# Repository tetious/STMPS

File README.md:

STMPS
=====

**STMPS** is a WIP 3d printer board based around the STM32f411, with inspiration and guidance
from the Printrboard, RAMPS 1.4, and the RepRap project.

**ALPHA-3**

This board is intended to work with Ambroz Bizjak's astonishingly fantastic 
[aprinter](https://github.com/ambrop72/aprinter) firmware. Configuration files and guidance will be
provided once the board is further along.

STMPS is open source hardware, licensed under CC BY-SA. Copyright (C) 2016 Greg Lincoln.

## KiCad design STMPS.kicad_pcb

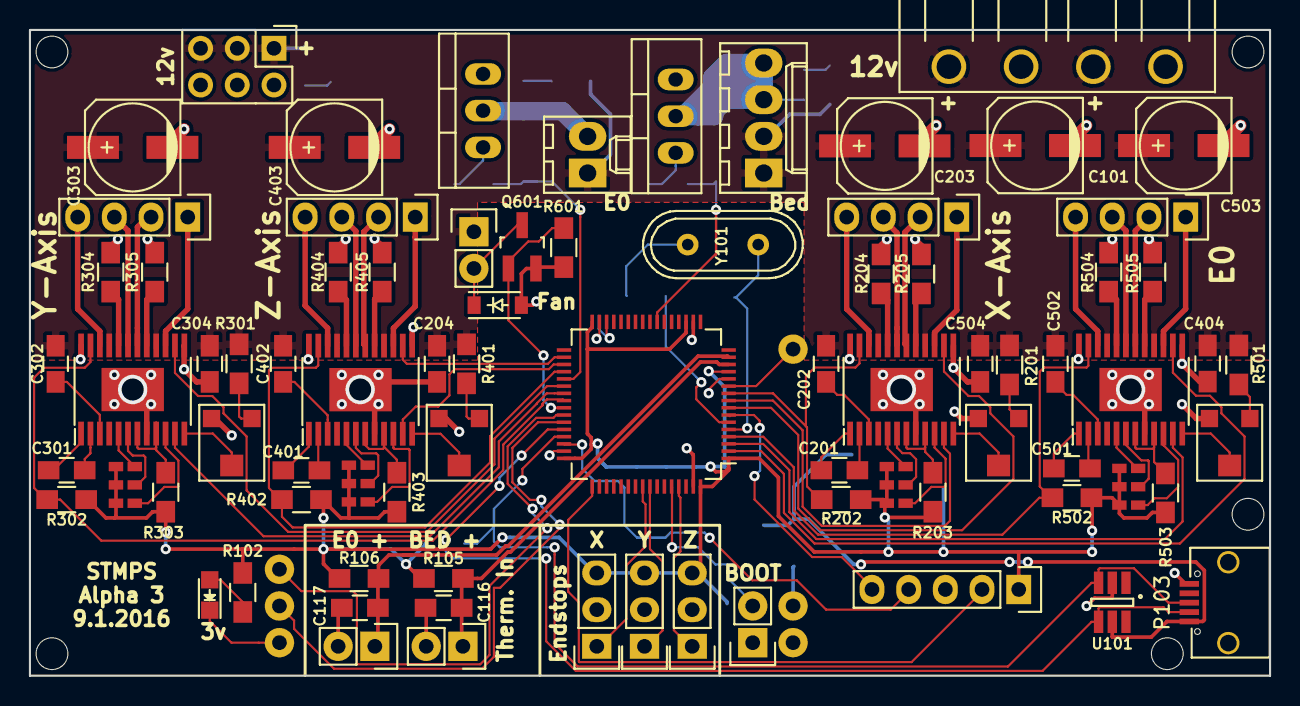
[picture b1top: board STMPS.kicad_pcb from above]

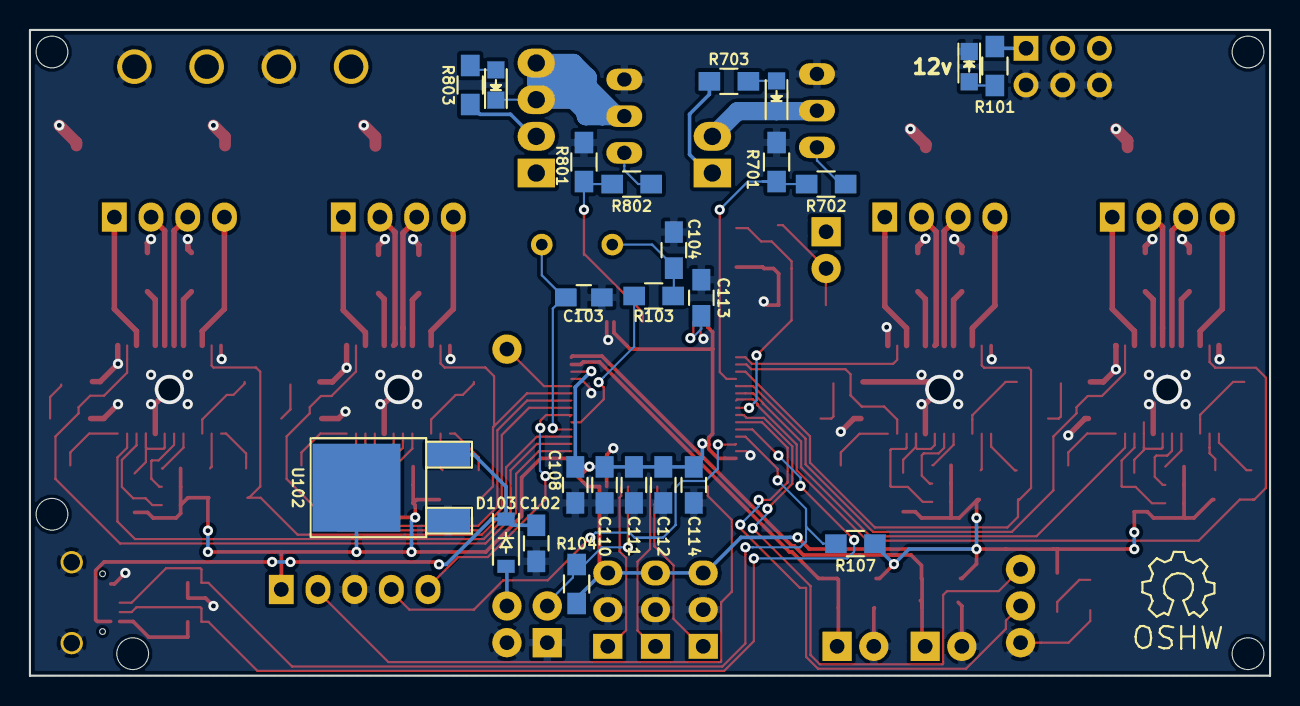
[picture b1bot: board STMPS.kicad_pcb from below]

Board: 2 copper layers, 85.9 x 44.7 mm, 113 parts (24 on the bottom side), 107 nets.

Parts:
C101, C203, C303, C403, C503: 100uf; c_elec_6.3x5.8
C102, C116, C117: 10uf; C_0805_HandSoldering
C103, C104: 20pf; C_0805_HandSoldering
C108, C110, C111, C112: 100nf; C_0805_HandSoldering
C113, C114: 4.7uf; C_0805_HandSoldering
C201, C202, C204, C301, C302, C304, C401, C402, C404, C501, C502, C504: 0.1uf; C_0805_HandSoldering
D101: 12v_PWR; LED_0805
D102: 3v_PWR; LED_0805
D103, D601: D_Schottky_Small; SOD-123
D701, D801: r; LED_0805
JP101: BOOT0; Pin_Header_Straight_1x02
JP201, JP301, JP401, JP501: MS3; MADW__SMD-solder-bridge-narrow
JP202, JP302, JP402, JP502: MS2; MADW__SMD-solder-bridge-narrow
JP203, JP303, JP403, JP503: MS1; MADW__SMD-solder-bridge-narrow
P101: 12v IN; 5EHDRC_1x04
P102: 12v; Pin_Header_Straight_2x03
P103: USB_OTG; USB_Micro-B-ebay
P104: E0_THERM; Pin_Header_Straight_1x02
P105: X_STOP; Pin_Header_Straight_1x03
P106: SWD; Pin_Header_Straight_1x05
P107: BED_THERM; Pin_Header_Straight_1x02
P108: Y_STOP; Pin_Header_Straight_1x03
P109: Z_STOP; Pin_Header_Straight_1x03
P110: BED; Molex_KK-6410-04_04x2.54mm_Straight
P111: EO; Molex_KK-6410-02_02x2.54mm_Straight
P201, P301, P401, P501: MOT; Pin_Header_Straight_1x04
P601: LP_OUT; Pin_Header_Straight_1x02
Q601: SSM3K333; SOT-23_Handsoldering
Q701, Q801: IPP039N04L; TO-220_Neutral123_Vertical
R101, R703, R803: 560; R_0805_HandSoldering
R102: 56; R_0805_HandSoldering
R103: 220; R_0805_HandSoldering
R104, R202, R203, R302, R303, R402, R403, R502, R503, R601, R701, R801: 100k; R_0805_HandSoldering
R105, R106, R107: 4.7k; R_0805_HandSoldering
R201, R301, R401, R501: 200k; R_0805_HandSoldering
R204, R205, R304, R305, R404, R405, R504, R505: 0.1; R_0805_HandSoldering
R702, R802: 100; R_0805_HandSoldering
RV201, RV301, RV401, RV501: 100k; BOURNS-TC33X-2
U101: AOZ8904; SOT-23-6_Handsoldering
U102: LM1117-3.3v; TO-252-2Lead
U103: STM32F411RCTx; LQFP-64_10x10mm_Pitch0.5mm
U105: CHIP-TOP; CHIP-MIN
U201, U301, U401, U501: A5984; TSSOP-24_4.4x7.8mm_Pitch0.65mm
Y101: Crystal; Crystal_HC49-U_Vertical

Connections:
+3.3v: C108.1, C110.1, C111.1, C112.1, C114.1, JP201.1, JP202.1, JP203.1, JP301.1, JP302.1, JP303.1, JP401.1, JP402.1, JP403.1, JP501.1, JP502.1, JP503.1, P105.3, P106.1, P108.3, P109.3, R102.2, R104.2, R105.1, R106.1, R107.1, R202.2, R203.2, R302.2, R303.2, R402.2, R403.2, R502.2, R503.2, U102.2, U103.1, U103.13, U103.19, U103.32, U103.48, U103.64
+12v: C101.1, C202.2, C203.1, C204.1, C302.2, C303.1, C304.1, C402.2, C403.1, C404.1, C502.2, C503.1, C504.1, P101.1, P101.3, P102.1, P102.3, P102.5, P110.1, P110.2, P111.1, P601.1, R101.2, R201.2, R301.2, R401.2, R501.2, R703.2, R803.2, U201.16, U201.21, U301.16, U301.21, U401.16, U401.21, U501.16, U501.21
/+5v: C102.1, D103.1, P103.1, U101.5, U102.3
/BED_FET/OUT-: D801.1, P110.3, P110.4, Q801.2
/BED_PWM: R801.1, R802.2, U103.23
/BED_THERM: C117.2, P107.1, R106.2, U103.15
/CHIP_1_WIRE: U103.11, U105.17
/E0_DIR: U103.2, U501.14
/E0_ENABLE: R502.1, U103.4, U501.23
/E0_FET/OUT-: D701.1, P111.2, Q701.2
/E0_PWM: R701.1, R702.2, U103.37
/E0_STEP: U103.3, U501.11
/E0_THERM: C116.2, P104.1, R105.2, U103.14
/FAN_PWM: Q601.1, R601.1, U103.41
/NRST: P106.5, U103.7
/SWCLK: P106.2, U103.49
/SWDIO: P106.4, U103.46
/USART1_RX: U103.43, U105.43
/USART1_TX: U103.42, U105.45
/USB_DM: P103.2, U101.4, U103.44
/USB_DP: P103.3, R107.2, U101.3, U103.45
/X_DIR: U103.8, U201.14
/X_ENABLE: R202.1, U103.10, U201.23
/X_STEP: U103.9, U201.11
/X_STOP: P105.1, U103.56
/Y_DIR: U103.38, U301.14
/Y_ENABLE: R302.1, U103.40, U301.23
/Y_STEP: U103.39, U301.11
/Y_STOP: P108.1, U103.57
/Z_DIR: U103.34, U401.14
/Z_ENABLE: R402.1, U103.36, U401.23
/Z_STEP: U103.35, U401.11
/Z_STOP: P109.1, U103.61
GND: C101.2, C102.2, C103.2, C104.2, C108.2, C110.2, C111.2, C112.2, C113.2, C114.2, C116.1, C117.1, C203.2, C204.2, C303.2, C304.2, C403.2, C404.2, C503.2, C504.2, D101.1, D102.1, D601.2, JP101.1, P101.2, P101.4, P102.2, P102.4, P102.6, P103.5, P103.6, P104.2, P105.2, P106.3, P107.2, P108.2, P109.2, Q601.2, Q701.3, Q801.3, R204.2, R205.2, R304.2, R305.2, R404.2, R405.2, R504.2, R505.2, R601.2, R701.2, R801.2, RV201.3, RV301.3, RV401.3, RV501.3, U101.2, U102.1, U103.12, U103.18, U103.31, U103.47, U103.63, U105.1, U105.41, U201.8, U201.13, U201.24, U201.T, U301.8, U301.13, U301.24, U301.T, U401.8, U401.13, U401.24, U401.T, U501.8, U501.13, U501.24, U501.T
unnamed: C103.1, U103.5, Y101.1
unnamed: C104.1, R103.2, Y101.2
unnamed: C113.1, U103.30
unnamed: C201.1, U201.1
unnamed: C201.2, U201.2
unnamed: C202.1, U201.3
unnamed: C301.1, U301.1
unnamed: C301.2, U301.2
unnamed: C302.1, U301.3
unnamed: C401.1, U401.1
unnamed: C401.2, U401.2
unnamed: C402.1, U401.3
unnamed: C501.1, U501.1
unnamed: C501.2, U501.2
unnamed: C502.1, U501.3
unnamed: D101.2, R101.1
unnamed: D102.2, R102.1
unnamed: D103.2, U105.3
unnamed: D601.1, P601.2, Q601.3
unnamed: D701.2, R703.1
unnamed: D801.2, R803.1
unnamed: JP101.2, R104.1, U103.60
unnamed: JP201.2, U201.10
unnamed: JP202.2, U201.6
unnamed: JP203.2, U201.5
unnamed: JP301.2, U301.10
unnamed: JP302.2, U301.6
unnamed: JP303.2, U301.5
unnamed: JP401.2, U401.10
unnamed: JP402.2, U401.6
unnamed: JP403.2, U401.5
unnamed: JP501.2, U501.10
unnamed: JP502.2, U501.6
unnamed: JP503.2, U501.5
unnamed: P201.1, U201.15
unnamed: P201.2, U201.18
unnamed: P201.3, U201.19
unnamed: P201.4, U201.22
unnamed: P301.1, U301.15
unnamed: P301.2, U301.18
unnamed: P301.3, U301.19
unnamed: P301.4, U301.22
unnamed: P401.1, U401.15
unnamed: P401.2, U401.18
unnamed: P401.3, U401.19
unnamed: P401.4, U401.22
unnamed: P501.1, U501.15
unnamed: P501.2, U501.18
unnamed: P501.3, U501.19
unnamed: P501.4, U501.22
unnamed: Q701.1, R702.1
unnamed: Q801.1, R802.1
unnamed: R103.1, U103.6
unnamed: R201.1, RV201.1
unnamed: R203.1, U201.7, U201.9
unnamed: R204.1, U201.20
unnamed: R205.1, U201.17
unnamed: R301.1, RV301.1
unnamed: R303.1, U301.7, U301.9
unnamed: R304.1, U301.20
unnamed: R305.1, U301.17
unnamed: R401.1, RV401.1
unnamed: R403.1, U401.7, U401.9
unnamed: R404.1, U401.20
unnamed: R405.1, U401.17
unnamed: R501.1, RV501.1
unnamed: R503.1, U501.7, U501.9
unnamed: R504.1, U501.20
unnamed: R505.1, U501.17
unnamed: RV201.2, U201.12
unnamed: RV301.2, U301.12
unnamed: RV401.2, U401.12
unnamed: RV501.2, U501.12

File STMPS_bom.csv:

Component,Description,Part,References,Value,Footprint,Quantity Per PCB,Datasheet,MPN
1,Unpolarized capacitor,C_Small,C108 C110 C111 C112 C201 C202 C204 C301 C302 C304 C401 C402 C404 C501 C502 C504,100nf,C_0805_HandSoldering,16,,
2,Polarised capacitor,CP_Small,C101,100uf,c_elec_6.3x5.8,1,,35TZV100M6.3X8
3,Polarised capacitor,CP1_Small,C203 C303 C403 C503,100uf,c_elec_6.3x5.8,4,,UWT1V101MCL1GS
4,Unpolarized capacitor,C_Small,C102 C116 C117,10uf,C_0805_HandSoldering,3,,
5,Unpolarized capacitor,C_Small,C103 C104,20pf,C_0805_HandSoldering,2,,
6,Unpolarized capacitor,C_Small,C113 C114,4.7uf,C_0805_HandSoldering,2,,
7,"LED, small symbol",LED_Small,D101,12v_PWR,LED_0805,1,,
8,"LED, small symbol",LED_Small,D102,3v_PWR,LED_0805,1,,
9,"Schottky diode, small symbol",D_Schottky_Small,D103 D601,D_Schottky_Small,SOD-123,2,,DB2X41100L DB2J41100L
10,"LED, small symbol",LED_Small,D701 D801,r,LED_0805,2,,
11,"Connector, single row, 01x02, pin header",CONN_01X02,JP101,BOOT0,Pin_Header_Straight_1x02,1,,
12,"Jumper, normally closed",Jumper_NC_Small,JP203 JP303 JP403 JP503,MS1,MADW__SMD-solder-bridge-narrow,4,,
13,"Jumper, normally closed",Jumper_NC_Small,JP202 JP302 JP402 JP502,MS2,MADW__SMD-solder-bridge-narrow,4,,
14,"Jumper, normally closed",Jumper_NC_Small,JP201 JP301 JP401 JP501,MS3,MADW__SMD-solder-bridge-narrow,4,,
15,"Connector, double row, 02x03, pin header",CONN_02X03,P102,12v,Pin_Header_Straight_2x03,1,,
16,"Connector, single row, 01x04, pin header",CONN_01X04,P101,12v IN,5EHDRC_1x04,1,,
17,"Connector, single row, 01x04, pin header",CONN_01X04,P110,BED,Molex_KK-6410-04_04x2.54mm_Straight,1,,
18,"Connector, single row, 01x02, pin header",CONN_01X02,P107,BED_THERM,Pin_Header_Straight_1x02,1,,
19,"Connector, single row, 01x02, pin header",CONN_01X02,P104,E0_THERM,Pin_Header_Straight_1x02,1,,
20,"Connector, single row, 01x02, pin header",CONN_01X02,P111,EO,Molex_KK-6410-02_02x2.54mm_Straight,1,,
21,"Connector, single row, 01x02, pin header",CONN_01X02,P601,LP_OUT,Pin_Header_Straight_1x02,1,,
22,"Connector, single row, 01x04, pin header",CONN_01X04,P201 P301 P401 P501,MOT,Pin_Header_Straight_1x04,4,,
23,"Connector, single row, 01x05, pin header",CONN_01X05,P106,SWD,Pin_Header_Straight_1x05,1,,
24,USB mini/micro connector,USB_OTG,P103,USB_OTG,USB_Micro-B-ebay,1,,
25,"Connector, single row, 01x03, pin header",CONN_01X03,P105,X_STOP,Pin_Header_Straight_1x03,1,,
26,"Connector, single row, 01x03, pin header",CONN_01X03,P108,Y_STOP,Pin_Header_Straight_1x03,1,,
27,"Connector, single row, 01x03, pin header",CONN_01X03,P109,Z_STOP,Pin_Header_Straight_1x03,1,,
28,Transistor N-MOSFET with substrate diode (general),Q_NMOS_GDS,Q701 Q801,IPP039N04L,TO-220_Neutral123_Vertical,2,,IPP039N04LGXKSA1-ND
29,Transistor N-MOSFETwith substrate diode (general),Q_NMOS_GSD,Q601,SSM3K333,SOT-23_Handsoldering,1,,SSM3K333RLFCT-ND
30,"Resistor, small symbol",R_Small,R204 R205 R304 R305 R404 R405 R504 R505,0.1,R_0805_HandSoldering,8,,
31,"Resistor, small symbol",R_Small,R702 R802,100,R_0805_HandSoldering,2,,
32,"Resistor, small symbol",R_Small,R104 R202 R203 R302 R303 R402 R403 R502 R503 R601 R701 R801,100k,R_0805_HandSoldering,12,,
33,"Resistor, small symbol",R_Small,R201 R301 R401 R501,200k,R_0805_HandSoldering,4,,
34,"Resistor, small symbol",R_Small,R103,220,R_0805_HandSoldering,1,,
35,"Resistor, small symbol",R_Small,R105 R106 R107,4.7k,R_0805_HandSoldering,3,,
36,"Resistor, small symbol",R_Small,R102,56,R_0805_HandSoldering,1,,
37,"Resistor, small symbol",R_Small,R101 R703 R803,560,R_0805_HandSoldering,3,,
38,Potentionmeter,POT,RV201 RV301 RV401 RV501,100k,BOURNS-TC33X-2,4,,TC33X-2-104E
39,,A5984,U201 U301 U401 U501,A5984,TSSOP-24_4.4x7.8mm_Pitch0.65mm,4,,A5984GLPTR-T
40,,AOZ8904,U101,AOZ8904,SOT-23-6_Handsoldering,1,,AOZ8904CIL
41,,CHIP-TOP,U105,CHIP-TOP,CHIP-MIN,1,,
42,,LM1117,U102,LM1117-3.3v,TO-252-2Lead,1,,
43,,STM32F411RCTx,U103,STM32F411RCTx,LQFP-64_10x10mm_Pitch0.5mm,1,,STM32F411RCT6
44,"Two pin crystal, small symbol",Crystal_Small,Y101,Crystal,Crystal_HC49-U_Vertical,1,,ABL-8.000MHZ-B2





Component Groups:,44
Component Count:,113
Fitted Components:,113
Number of PCBs:,1
Total components:,113
Schematic Version:,
Schematic Date:,
BoM Date:,Thu 20 Jul 2017 09:48:18 PM EDT
Schematic Source:,/home/greg/Boards/STMPS/STMPS.sch
KiCad Version:,Eeschema 4.0.7-e0-6372~58~ubuntu16.04.1

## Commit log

2016-07-31 Initial checkin.
2016-08-01 Possibly finished schematic.
2016-08-01 Add readme.
2016-08-01 Move datasheets to a subfolder.
2016-08-01 Start working on footprint assignments.
2016-08-02 Finish assigning footprints.
2016-08-02 Fix jumper names for steppers. Start prepping for layout.
2016-08-03 Complete routing, first pass.
2016-08-03 Cleanup silkscreen and other minor tweaks.
2016-08-04 Fixed incorrect clock configuration.
2016-08-04 Corrected resistors and rail for vREF.
2016-08-04 Finalized layout for Alpha 1.
2016-08-07 Fix USB connection. Cleanups.
2016-08-08 WIP rev B.
2016-08-08 Alpha 2 board layout.
2016-08-14 Minor cleanups.
2016-08-24 Hopefully fix issue with mask/pour clearance.
    Correctly tie VREF+ to VCC.
2016-08-31 Alpha 3. Fix solder mask clearance. Fix 3.3v not tied to ref+. Tweaks and cleanups.
2016-08-31 A few more tweaks.
2016-08-31 Add board image.
2020-05-09 Update stuff. ;)
